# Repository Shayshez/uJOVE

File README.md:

# uJOVE
# CC BY-NC-SA 4.0
## Micro version of JOVE - Multimode filter, originally by System 80
## Warning for DIY beginners - this project is a hard to build with dense PCB and low pitch ic's which requires experience in SMD soldering.
### If you care about this project - DO NOT SELL ASSEMBLED MODULES, Build only for your own use!

Interactive BOM: http://diy.plum-audio.com/projects/uJove/iBom/

Plum Audio uJove is 8hp version of Jove - Multimode filter By System 80 that is inspired by the Roland Jupiter 6 filter.

uJuve is exactly the same circuit as the original 14 hp Juve with the same amazing sound. 

2 extra modifications have been added to increase the sound variety:

1. When no jack is plugged in to input 2 Positive feedback from the output to input 2 is activated. the feedback level can be controlled by LEVEL 2 knob.
2. Input 2 level knob can add 6dB of gain, 0dB on the middle, +6dB (clipping) when fully clockwise. 

4 Leds of the original 14 hp Jove replaced by one RGB Led

Modes colours:
RED - LP24 , ORANGE - LP12 , BLUE - BP , GREEN - HP

### About Positive Feedback:
Resonance = inverted feedback 

Positive feedback should distort the signal.

In LP2/4 modes (red/orange) the positive feedback alone can make pulses.

it’s better to mix between positive and negative feedback to achieve distorted worm sound.
Also try to use input 2 in LP modes and the positive feedback become clipper (attenuation until middle position of the knob and clipping from middle position)

The positive feedback sounds much better in BP/HP modes (blue/green) to achive great distortion.

uJove is available only as DIY project, for pcb's and panels: https://pushermanproductions.com/product/plum-audio-ujove-pcb-and-8hp-aluminium-panel/

Assembling Video (Part 1): https://www.youtube.com/watch?v=_F6PMT1OO5I

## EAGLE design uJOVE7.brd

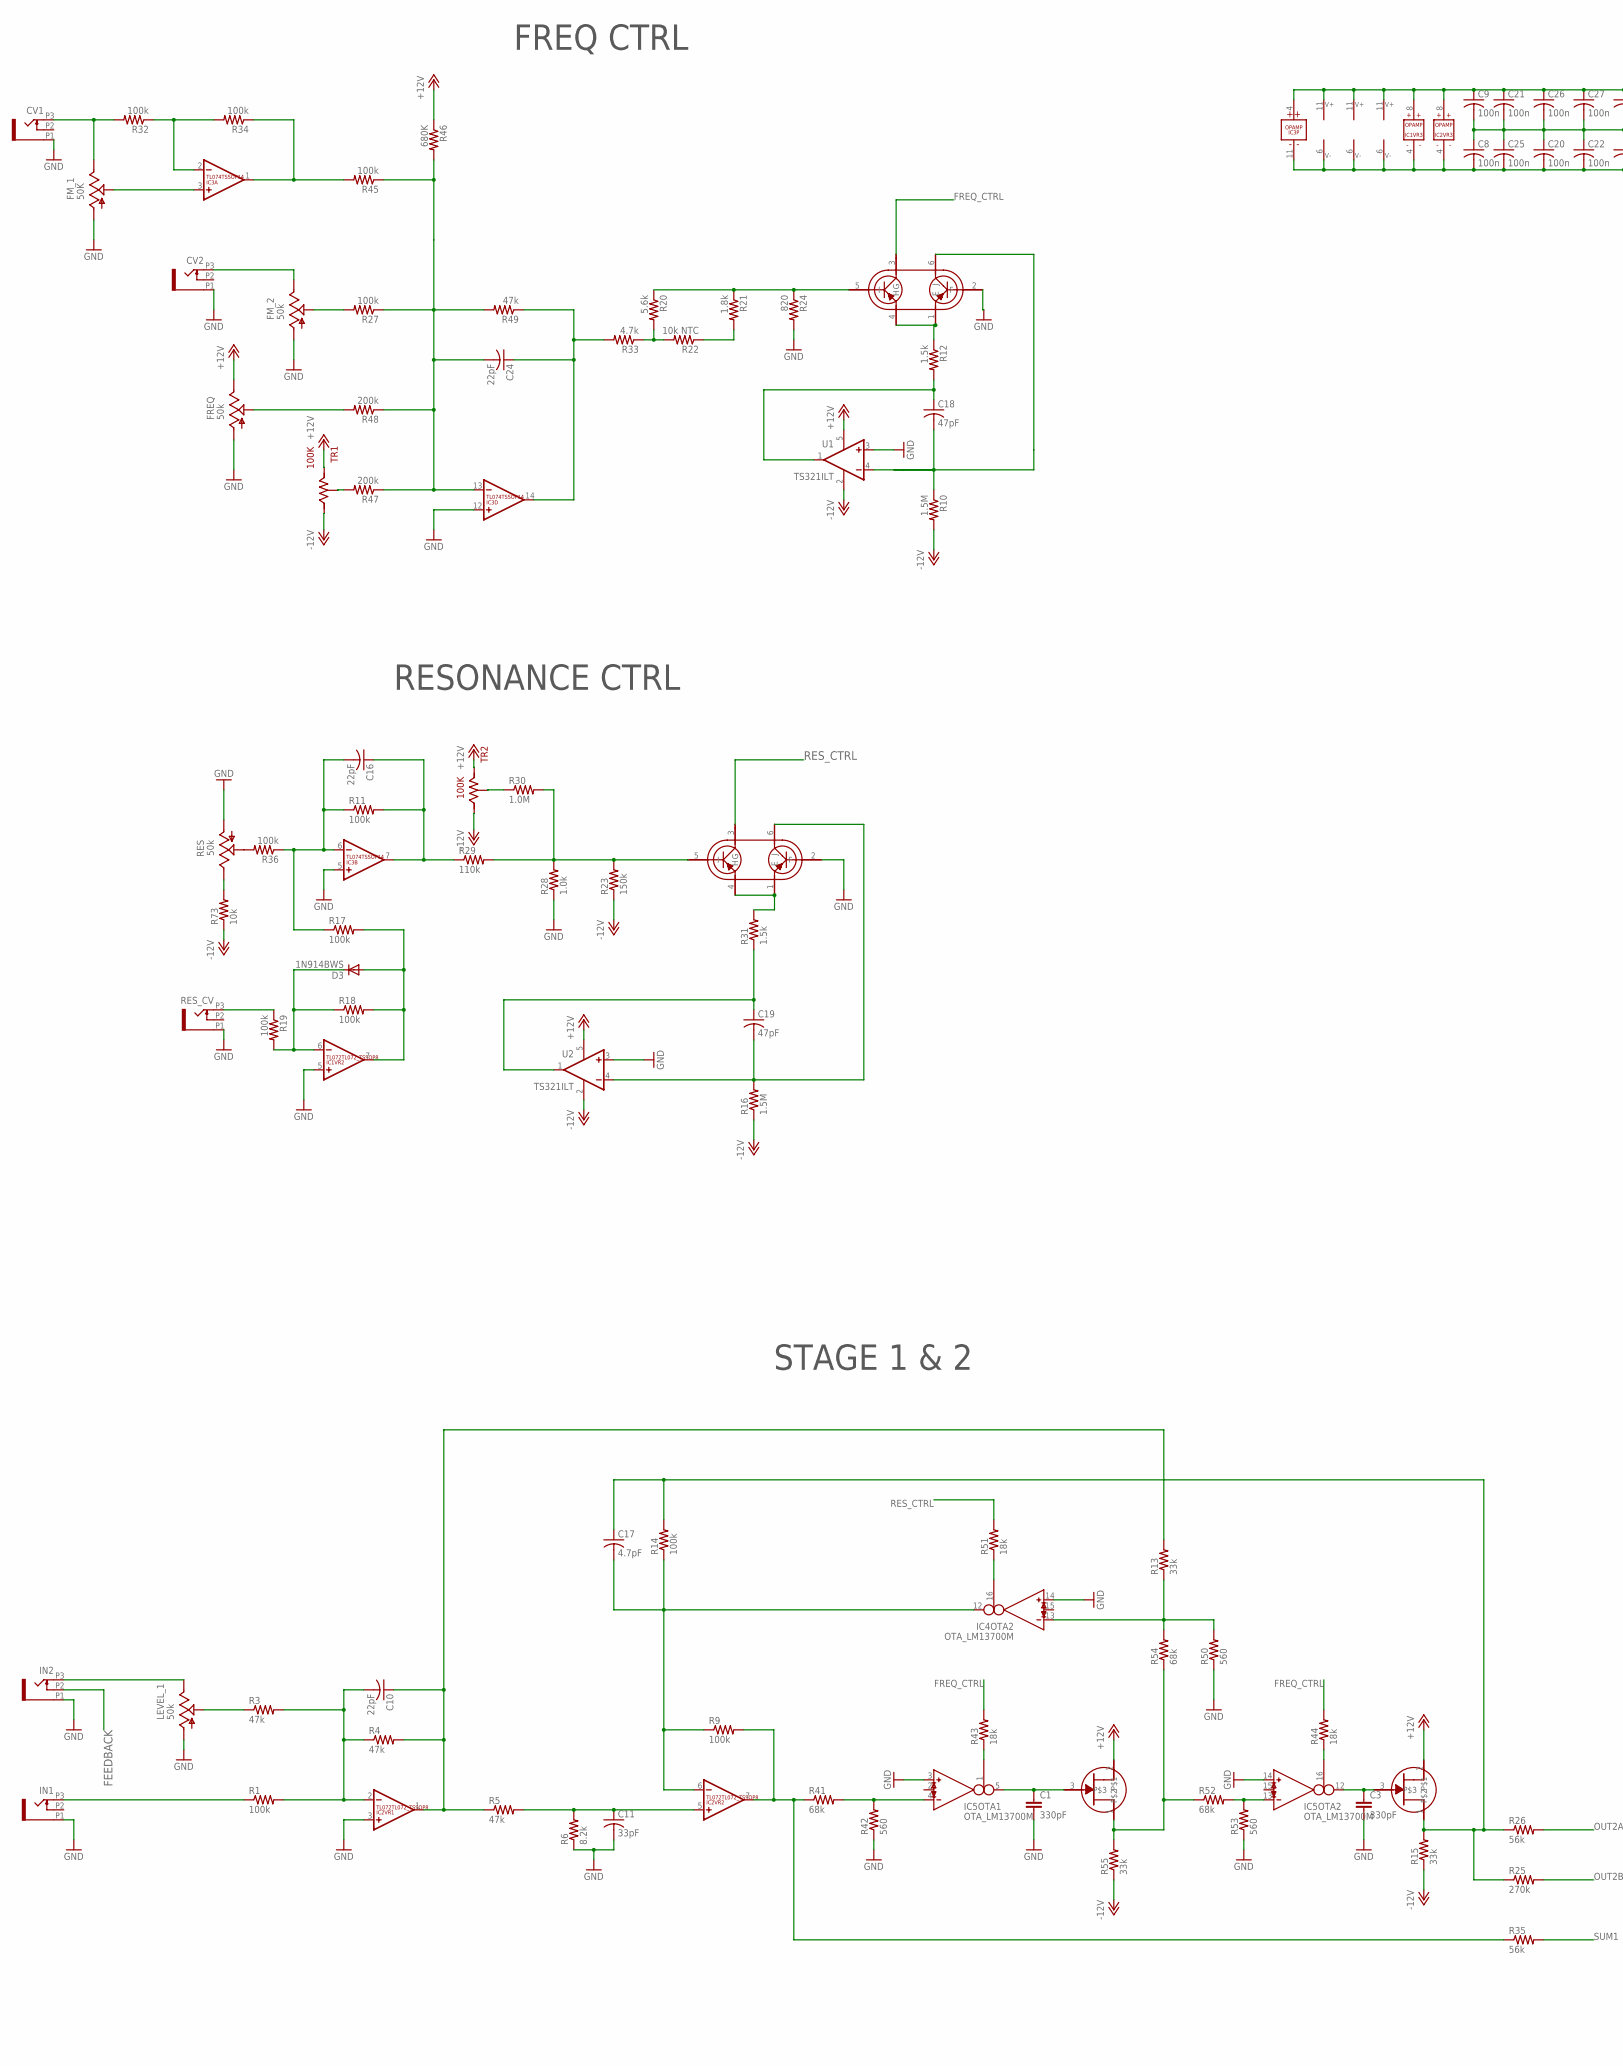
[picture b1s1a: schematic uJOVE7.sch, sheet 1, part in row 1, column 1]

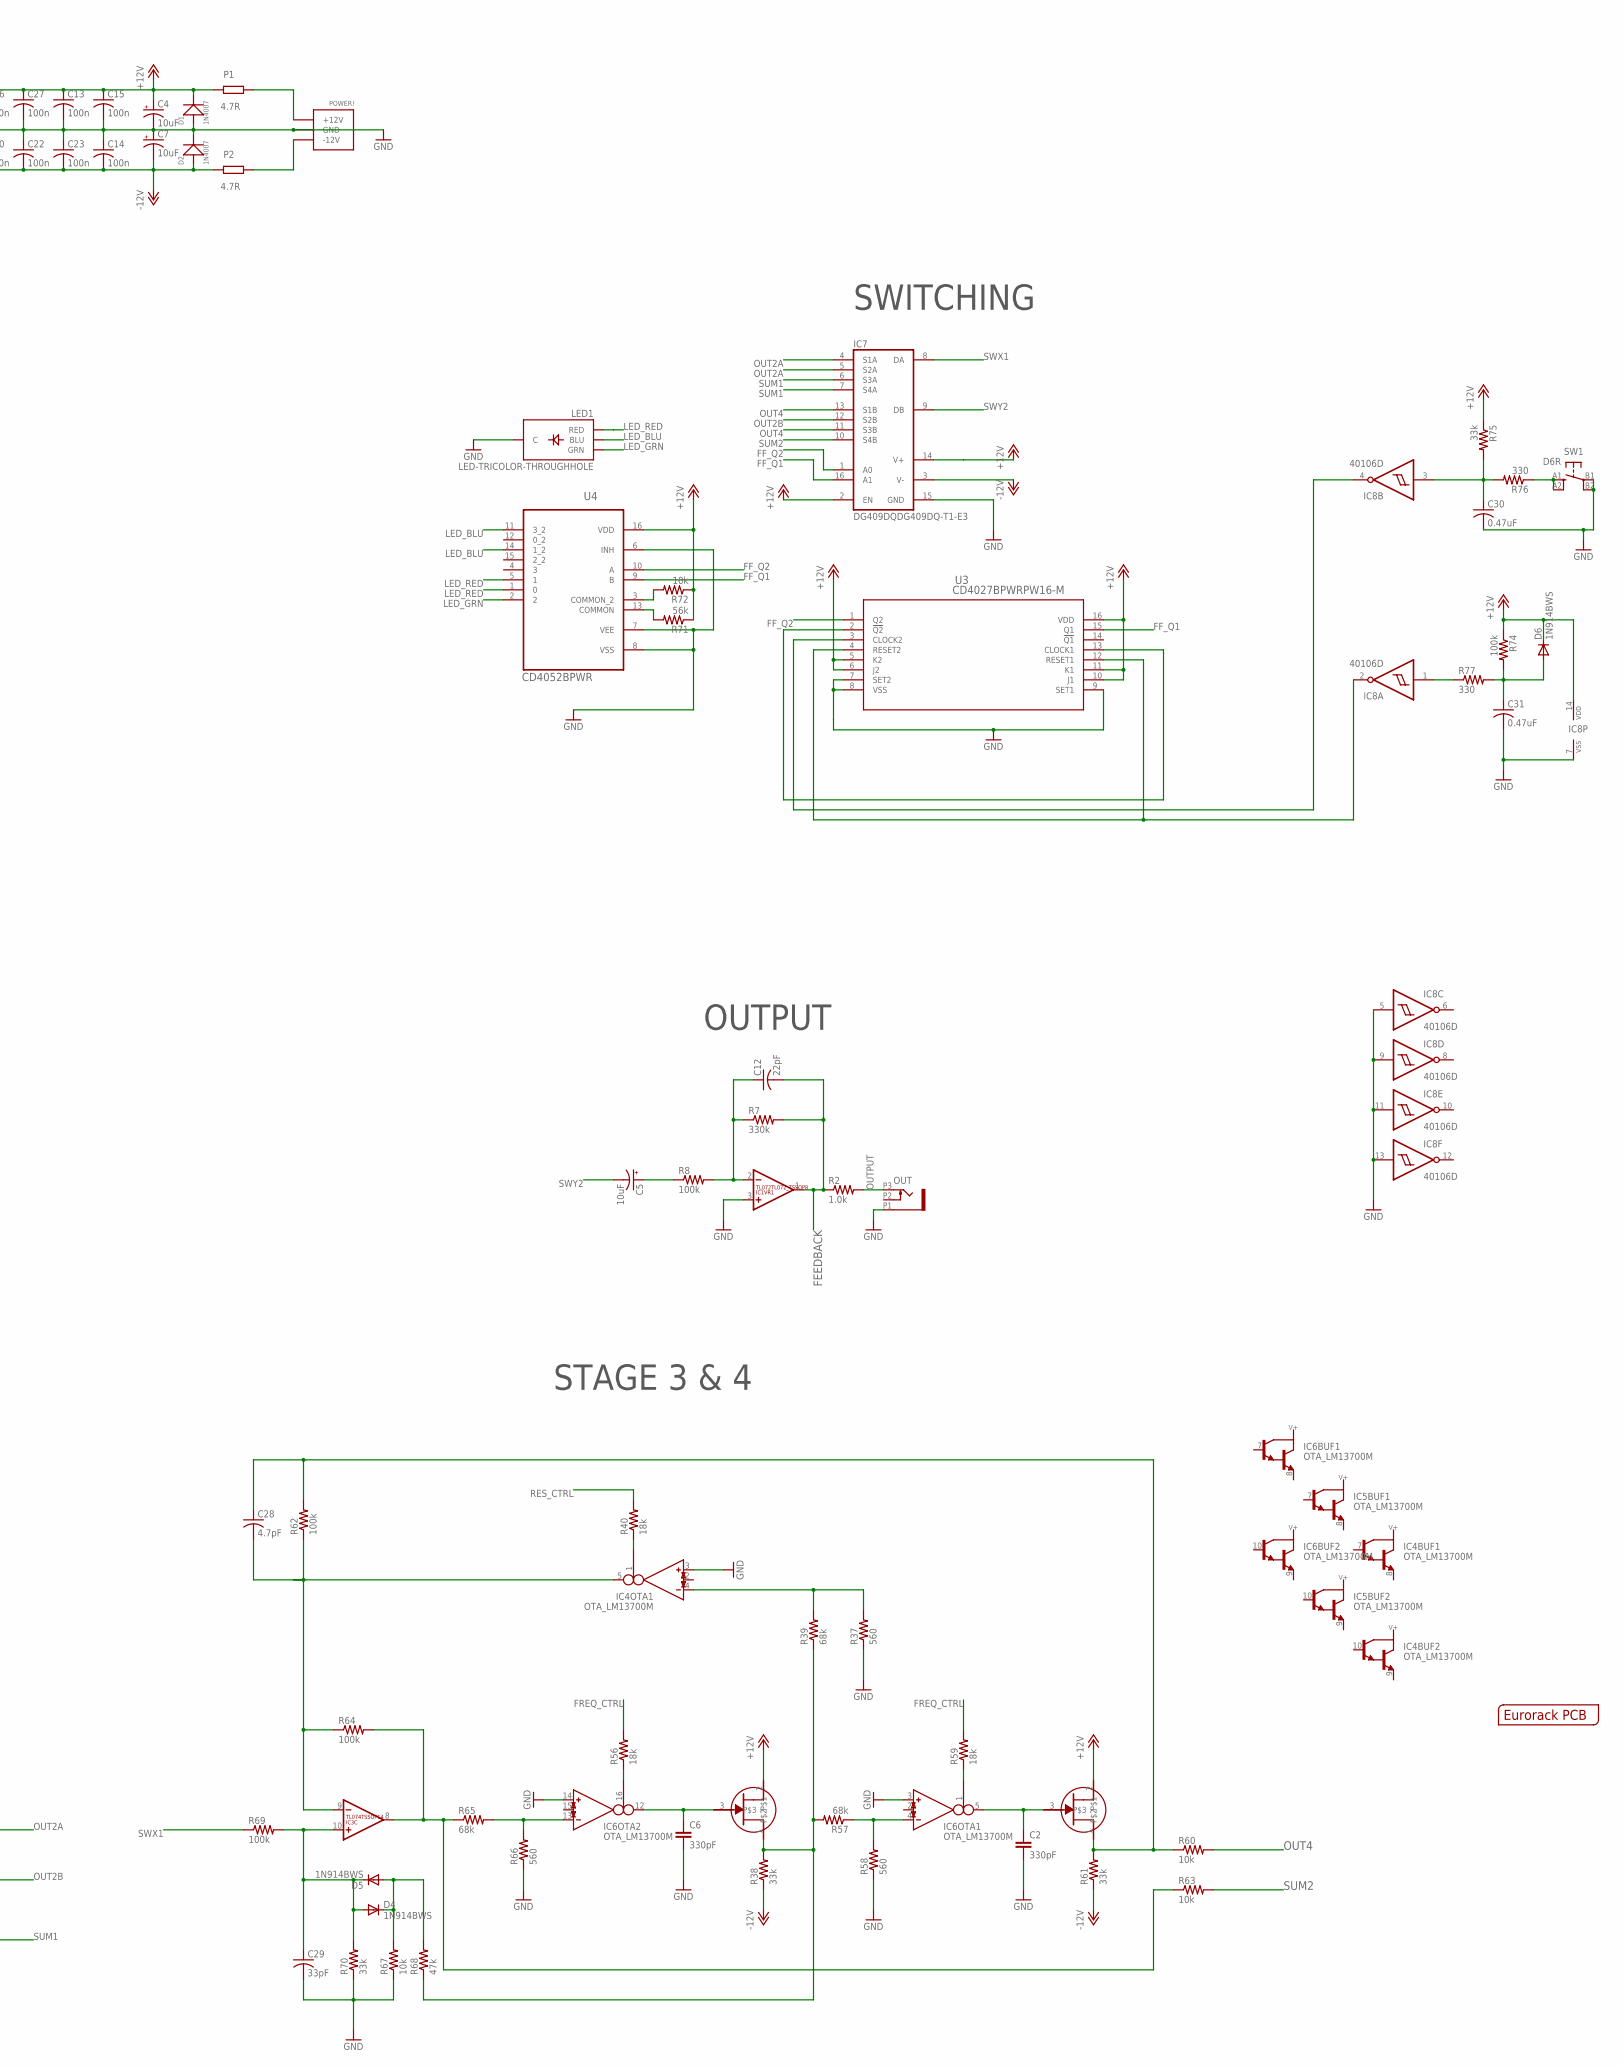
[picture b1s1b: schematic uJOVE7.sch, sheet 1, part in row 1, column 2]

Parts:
C1, C2, C3, C6: 330pF; C5B5
C4, C5, C7: 10uF; PANASONIC_C
C8, C9, C13, C14, C15, C20, C21, C22, C23, C25, C26, C27: 100n; C0603
C10, C12, C16, C24: 22pF; C0603
C11, C29: 33pF; C0603
C17, C28: 4.7pF; C0603
C18, C19: 47pF; C0603
C30, C31: 0.47uF; C0603
CV1, CV2: OG-PJ301_PJ301_THONKICONN; OG-PJ301_WQP_PJ_301M6_NO_HOLE
D1, D2: 1N4007; DO-214AC
D3, D4, D5, D6: 1N914BWS; SOD323-R
FM_1: 50K; OG-POTS_ALPS_POT_VERTICAL
FM_2: 50k; OG-POTS_ALPS_POT_VERTICAL
FREQ: 50k; OG-POTS_ALPS_POT_VERTICAL_PS
IC1, IC2: TL072TL072_TSSOP8; TL072_TSSOP8
IC3: TL074TSSOP14; TSSOP14
IC4, IC5, IC6: OTA_LM13700M; OTA_SO16
IC7: DG409DQDG409DQ-T1-E3; TSSOP16
IC8: 40106D; SO14
IN1, IN2: OG-PJ301_PJ301_THONKICONN; OG-PJ301_WQP_PJ_301M6_NO_HOLE
LED1: LED-TRICOLOR-THROUGHHOLE
LEVEL_1: 50k; OG-POTS_ALPS_POT_VERTICAL
OUT: OG-PJ301_PJ301_THONKICONN; OG-PJ301_WQP_PJ_301M6_NO_HOLE
P1, P2: 4.7R; R1206
PCB1: EURORACK_PCB; EURORACK8HPPCB-S
POWER!: POWER_SIMPLE; 2X05_SMT_HEADER
Q1, Q2: BCM857BS; SOT65P210X110-6N
Q3, Q4, Q5, Q6: MMBFJ112MMBFJ112; SOT23
R1, R8, R9, R11, R14, R17, R18, R19, R27, R32, R34, R36, R45, R62, R64, R69, R74: 100k; R0603
R2, R28: 1.0k; R0603
R3, R4, R5, R49, R68: 47k; R0603
R6: 8.2k; R0603
R7: 330k; R0603
R10, R16: 1.5M; R0603
R12, R31: 1.5k; R0603
R13, R15, R38, R55, R61, R70, R75: 33k; R0603
R20: 5.6k; R0603
R21: 1.8k; R0603
R22: 10k NTC; R0805
R23: 150k; R0603
R24: 820; R0603
R25: 270k; R0603
R26, R35, R71: 56k; R0603
R29: 110k; R0603
R30: 1.0M; R0603
R33: 4.7k; R0603
R37, R42, R50, R53, R58, R66: 560; R0603
R39, R41, R52, R54, R57, R65: 68k; R0603
R40, R43, R44, R51, R56, R59: 18k; R0603
R46: 680K; R0603
R47, R48: 200k; R0603
R60, R63, R67, R72, R73: 10k; R0603
R76, R77: 330; R0603
RES: 50k; OG-POTS_ALPS_POT_VERTICAL_PS
RES_CV: OG-PJ301_PJ301_THONKICONN; OG-PJ301_WQP_PJ_301M6_NO_HOLE
SW1: D6R
TR1, TR2: 100K; TC33X-2
U1, U2: TS321ILT; SOT23-5
U3: CD4027BPWRPW16-M; PW16-M
U4: CD4052BPWR; SOP65P640X120-16N

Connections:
+12V: C4.+, C9.1, C13.1, C15.1, C21.1, C26.1, C27.1, D1.2 (-), D6.C, FREQ.P$1 (E), IC1.8 (V+), IC2.8 (V+), IC3.4 (V+), IC4.11 (V+), IC5.11 (V+), IC6.11 (V+), IC7.2 (EN), IC7.14 (V+), IC8.14 (VDD), P1.1, Q3.2, Q4.2, Q5.2, Q6.2, R46.1, R71.1, R72.1, R74.1, R75.1, TR1.1, TR2.1, U1.5 (V+), U2.5 (V+), U3.5 (K2), U3.6 (J2), U3.10 (J1), U3.11 (K1), U3.16 (VDD), U4.16 (VDD)
-12V: C7.-, C8.2, C14.2, C20.2, C22.2, C23.2, C25.2, D2.1 (+), IC1.4 (V-), IC2.4 (V-), IC3.11 (V-), IC4.6 (V-), IC5.6 (V-), IC6.6 (V-), IC7.3 (V-), P2.1, R10.2, R15.1, R16.1, R23.1, R38.1, R55.1, R61.1, R73.1, TR1.3, TR2.3, U1.2 (V-), U2.2 (V-)
FEEDBACK: C12.2, IC1.1 (OUT), IN2.P2 (2), R2.1, R7.2
FF_Q1: IC7.16 (A1), U3.15 (Q1), U4.9 (B)
FF_Q2: IC7.1 (A0), U3.1 (Q2), U4.10 (A)
FREQ_CTRL: Q1.3 (G), R43.2, R44.2, R56.2, R59.2
GND: C1.2, C2.2, C3.2, C4.-, C6.2, C7.+, C8.1, C9.2, C11.2, C13.2, C14.1, C15.2, C20.1, C21.2, C22.1, C23.1, C25.1, C26.2, C27.2, C29.2, C30.2, C31.2, CV1.P1 (1), CV2.P1 (1), D1.1 (+), D2.2 (-), FM_1.P$3 (A), FM_2.P$3 (A), FREQ.P$3 (A), IC1.3 (+IN), IC1.5 (+IN), IC2.3 (+IN), IC3.5 (+IN), IC3.12 (+IN), IC4.3 (IN_P), IC4.14 (IN_P), IC5.3 (IN_P), IC5.14 (IN_P), IC6.3 (IN_P), IC6.14 (IN_P), IC7.15 (GND), IC8.5 (I), IC8.7 (VSS), IC8.9 (I), IC8.11 (I), IC8.13 (I), IN1.P1 (1), IN2.P1 (1), LED1.GND (C), LEVEL_1.P$3 (A), OUT.P1 (1), POWER!.3 (GND), POWER!.4 (GND), POWER!.5 (GND), POWER!.6 (GND), POWER!.7 (GND), POWER!.8 (GND), Q1.2 (F), Q2.2 (F), R6.1, R24.2, R28.1, R37.1, R42.1, R50.1, R53.1, R58.1, R66.1, R67.1, R70.1, RES.P$3 (A), RES_CV.P1 (1), SW1.B1, SW1.B2 (P1), U1.3 (+IN), U2.3 (+IN), U3.7 (SET2), U3.8 (VSS), U3.9 (SET1), U4.6 (INH), U4.7 (VEE), U4.8 (VSS)
LED_BLU: LED1.BLU, U4.11 (3_2), U4.14 (1_2)
LED_GRN: LED1.GRN, U4.2
LED_RED: LED1.RED, U4.1 (0), U4.5 (1)
unnamed: P1.2, POWER!.9 (+12V), POWER!.10 (+12V)
unnamed: P2.2, POWER!.1 (-12V), POWER!.2 (-12V)
unnamed: IN1.P3 (3), R1.1
unnamed: C10.2, IC2.2 (-IN), R1.2, R3.2, R4.1
unnamed: IN2.P3 (3), LEVEL_1.P$1 (E)
unnamed: LEVEL_1.P$2 (S), R3.1
unnamed: C10.1, IC2.1 (OUT), R4.2, R5.1, R13.2
unnamed: C11.1, IC2.5 (+IN), R5.2, R6.2
unnamed: IC2.7 (OUT), R9.2, R35.1, R41.1
unnamed: C17.2, IC2.6 (-IN), IC4.12 (OUT), R9.1, R14.1
unnamed: IC5.4 (IN_N), R41.2, R42.2
unnamed: IC5.1 (I_BIAS), R43.1
unnamed: C1.1, IC5.5 (OUT), Q4.3
unnamed: IC5.13 (IN_N), R52.2, R53.2
unnamed: IC4.13 (IN_N), R13.1, R50.2, R54.2
unnamed: IC4.16 (I_BIAS), R51.1
unnamed: C17.1, Q3.1, R14.2, R15.2, R25.1, R26.1
unnamed: Q4.1, R52.1, R54.1, R55.2
unnamed: IC5.16 (I_BIAS), R44.1
unnamed: R73.2, RES.P$1 (E)
unnamed: C3.1, IC5.12 (OUT), Q3.3
unnamed: C5.+, R8.1
unnamed: C12.1, IC1.2 (-IN), R7.1, R8.2
unnamed: C31.1, D6.A, R74.2, R77.2
unnamed: IC3.8 (OUT), R63.1, R64.2, R65.1
unnamed: IC6.4 (IN_N), R57.1, R58.2
unnamed: D4.C, D5.A, R67.2, R68.2
unnamed: C29.1, D4.A, D5.C, IC3.10 (+IN), R69.2, R70.2
unnamed: IC6.13 (IN_N), R65.2, R66.2
unnamed: IC4.4 (IN_N), R37.2, R39.2
unnamed: IC6.16 (I_BIAS), R56.1
unnamed: C6.1, IC6.12 (OUT), Q6.3
unnamed: Q6.1, R38.2, R39.1, R57.2, R68.1
unnamed: IC4.1 (I_BIAS), R40.1
unnamed: C28.2, IC3.9 (-IN), IC4.5 (OUT), R62.1, R64.1
unnamed: R36.2, RES.P$2 (S)
unnamed: IC6.1 (I_BIAS), R59.1
unnamed: C28.1, Q5.1, R60.1, R61.2, R62.2
unnamed: C2.1, IC6.5 (OUT), Q5.3
unnamed: R19.1, RES_CV.P3 (3)
unnamed: D3.C, IC1.6 (-IN), R18.1, R19.2
unnamed: D3.A, IC1.7 (OUT), R17.2, R18.2
unnamed: C16.2, IC3.6 (-IN), R11.1, R17.1, R36.1
unnamed: R30.1, TR2.2
unnamed: C16.1, IC3.7 (OUT), R11.2, R29.1
unnamed: Q2.5 (I), R23.2, R28.2, R29.2, R30.2
unnamed: Q2.1 (E), Q2.4 (H), R31.2
unnamed: C19.2, Q2.6 (J), R16.2, U2.4 (-IN)
unnamed: C19.1, R31.1, U2.1 (OUT)
unnamed: CV1.P3 (3), FM_1.P$1 (E), R32.2
unnamed: IC3.2 (-IN), R32.1, R34.2
unnamed: FM_1.P$2 (S), IC3.3 (+IN)
unnamed: IC3.1 (OUT), R34.1, R45.2
unnamed: C24.2, IC3.13 (-IN), R27.1, R45.1, R46.2, R47.1, R48.1, R49.2
unnamed: CV2.P3 (3), FM_2.P$1 (E)
unnamed: FM_2.P$2 (S), R27.2
unnamed: FREQ.P$2 (S), R48.2
unnamed: R47.2, TR1.2
unnamed: C24.1, IC3.14 (OUT), R33.2, R49.1
unnamed: R20.2, R22.2, R33.1
unnamed: Q1.5 (I), R20.1, R21.1, R24.1
unnamed: R21.2, R22.1
unnamed: C18.2, Q1.6 (J), R10.1, U1.4 (-IN)
unnamed: Q1.1 (E), Q1.4 (H), R12.1
unnamed: C18.1, R12.2, U1.1 (OUT)
unnamed: IC8.1 (I), R77.1
unnamed: C30.1, IC8.3 (I), R75.2, R76.2
unnamed: IC8.2 (O), U3.4 (RESET2), U3.12 (RESET1)
unnamed: IC8.4 (O), U3.3 (CLOCK2)
unnamed: R76.1, SW1.A1 (S), SW1.A2 (S1)
unnamed: U3.2 (!Q2), U3.13 (CLOCK1)
unnamed: R72.2, U4.3 (COMMON_2)
unnamed: R71.2, U4.13 (COMMON)
OUT2A: IC7.4 (S1A), IC7.5 (S2A), R26.2
OUT2B: IC7.12 (S2B), R25.2
OUT4: IC7.11 (S3B), IC7.13 (S1B), R60.2
OUTPUT: OUT.P3 (3), R2.2
RES_CTRL: Q2.3 (G), R40.2, R51.2
SUM1: IC7.6 (S3A), IC7.7 (S4A), R35.2
SUM2: IC7.10 (S4B), R63.2
SWX1: IC7.8 (DA), R69.1
SWY2: C5.-, IC7.9 (DB)

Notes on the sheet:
STAGE 1 & 2
OUTPUT
STAGE 3 & 4
RESONANCE CTRL
FREQ CTRL
SWITCHING

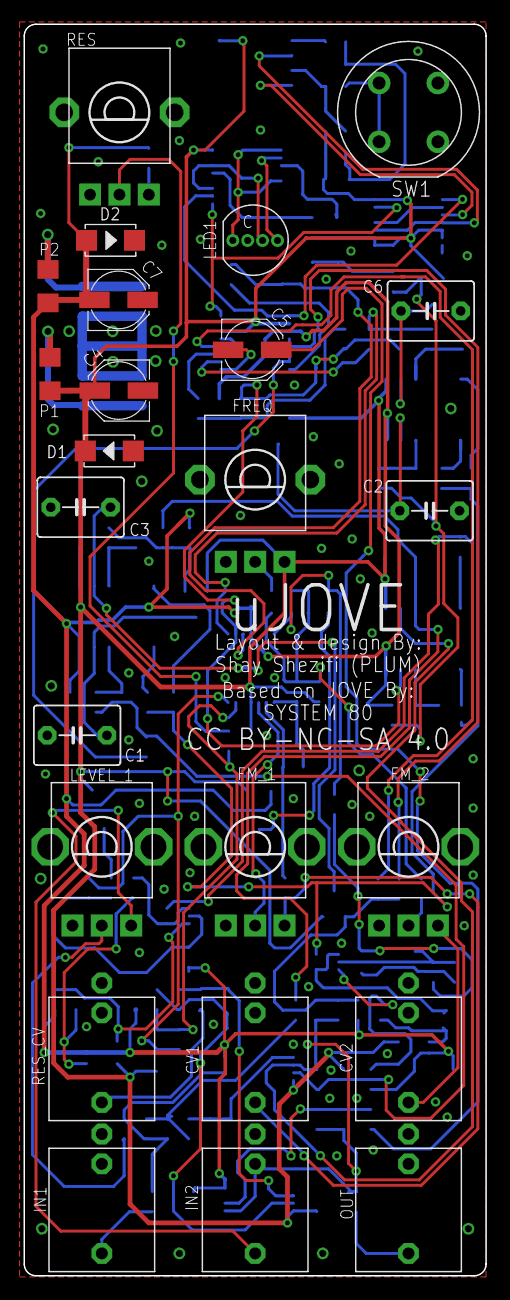
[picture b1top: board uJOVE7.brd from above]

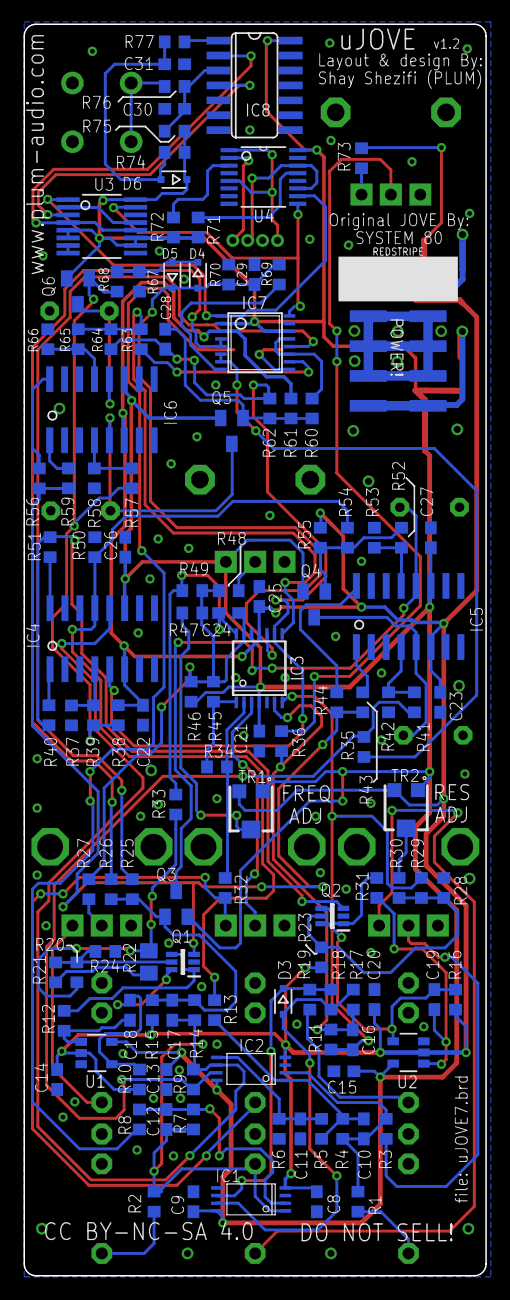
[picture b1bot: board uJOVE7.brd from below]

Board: 2 copper layers, 39.3 x 106.5 mm, 151 parts (126 on the bottom side), 92 nets.

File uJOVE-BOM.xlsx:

Qty | Parts | Value | Device | Package | Mouser referance | Description
 | CAPS
2 | C15, C26 | 4.7pF | C-USC0603 | C0603 | CC0603CRNPO9BN4R7 | CAPACITOR, American symbol
4 | C8, C10, C14, C22 | 22pF | C-USC0603 | C0603 | C0603C220J5G7411 | CAPACITOR, American symbol
2 | C9, C27 | 33pF | C-USC0603 | C0603 | C0603C330J5GACTU | CAPACITOR, American symbol
2 | C16, C17 | 47pF | C-USC0603 | C0603 | C0603C470J5GACTU | CAPACITOR, American symbol
10 | C11, C12, C13, C18, C19, C20, C21, C23, C24, C25 | 100n | C-USC0603 | C0603 | C0603C104M5RACTU | CAPACITOR, American symbol
2 | C28, C29 | 0.47uF | C-USC0603 | C0603 | CGA3E3X5R1H474MB | CAPACITOR, American symbol
1 | C5 | 10uF | CPOL-USC | PANASONIC_C | UUQ1E100MCL1GB | POLARIZED CAPACITOR, American symbol
2 | C4, C7 | 10uF | CPOL-USC | PANASONIC_C | EEE-1EA100SR | POLARIZED CAPACITOR, American symbol
4 | C1, C2, C3, C6 | 330pF | C5/5 | C5B5 | PFR5331J100J11L4 | Polypropylene FILM CAPACITOR 5mm
 | RESISTORS
2 | R76, R77 | 330 | R-US_R0603 | R0603 | RC0603FR-07330RL | RESISTOR, American symbol
6 | R37, R42, R50, R53, R57, R65 | 560 | R-US_R0603 | R0603 | RC0603FR-07560RL | RESISTOR, American symbol
1 | R24 | 820 | R-US_R0603 | R0603 | RC0603FR-07820RL | RESISTOR, American symbol
2 | R2, R28 | 1.0k | R-US_R0603 | R0603 | RC0603FR-071KL | RESISTOR, American symbol
2 | R12, R31 | 1.5k | R-US_R0603 | R0603 | RC0603FR-071K5L | RESISTOR, American symbol
1 | R21 | 1.8k | R-US_R0603 | R0603 | RC0603FR-071K8L | RESISTOR, American symbol
1 | R33 | 4.7k | R-US_R0603 | R0603 | RC0603FR-074K7L | RESISTOR, American symbol
1 | R20 | 5.6k | R-US_R0603 | R0603 | RC0603FR-105K6L | RESISTOR, American symbol
1 | R6 | 8.2k | R-US_R0603 | R0603 | RC0603FR-078K2L | RESISTOR, American symbol
5 | R59, R62, R67, R72, R73 | 10k | R-US_R0603 | R0603 | RC0603FR-0710KL | RESISTOR, American symbol
6 | R40, R43, R44, R51, R58, R66 | 18k | R-US_R0603 | R0603 | RC0603FR-0718KL | RESISTOR, American symbol
7 | R13, R15, R38, R55, R60, R70, R75 | 33k | R-US_R0603 | R0603 | RC0603FR-0733KL | RESISTOR, American symbol
5 | R3, R4, R5, R49, R68 | 47k | R-US_R0603 | R0603 | RC0603FR-0747KL | RESISTOR, American symbol
3 | R26, R35, R71 | 56k | R-US_R0603 | R0603 | RC0603FR-0756KL | RESISTOR, American symbol
6 | R39, R41, R52, R54, R56, R64 | 68k | R-US_R0603 | R0603 | RC0603FR-0768KL | RESISTOR, American symbol
17 | R1, R8, R9, R11, R14, R17, R18, R19, R27, R32, R34, R36, R45, R61, R63, R69, R74 | 100k | R-US_R0603 | R0603 | RC0603FR-07100KL | RESISTOR, American symbol
1 | R29 | 110k | R-US_R0603 | R0603 | RC0603FR-07110KL | RESISTOR, American symbol
1 | R23 | 150k | R-US_R0603 | R0603 | RC0603FR-07150KL | RESISTOR, American symbol
2 | R47, R48 | 200k | R-US_R0603 | R0603 | RC0603FR-07200KL | RESISTOR, American symbol
1 | R25 | 270k | R-US_R0603 | R0603 | RC0603FR-07270KL | RESISTOR, American symbol
1 | R7 | 330k | R-US_R0603 | R0603 | RC0603FR-07330KL | RESISTOR, American symbol
1 | R46 | 680K | R-US_R0603 | R0603 | RC0603FR-07680KL | RESISTOR, American symbol
1 | R30 | 1.0M | R-US_R0603 | R0603 | RC0603FR-071ML | RESISTOR, American symbol
2 | R10, R16 | 1.5M | R-US_R0603 | R0603 | RC0603FR-071M5L | RESISTOR, American symbol
1 | R22 | 10k NTC | R-US_R0805 | R0805 | NCP21XV103J03RA | RESISTOR, American symbol
 | Note1: R71 & R72 = led brightness, R71 for green, R72 for red & blue.
 | Note2: R3 = Gain of input 2 and feadback, 47k for 0dB at pot middle position an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
 | DIODES / TRANSISTORS
2 | P1, P2 | PTCSMD | PTCSMD | PTC-1206 | 1206L035/16YR | Resettable Fuse PTC
4 | D3, D4, D5, D6 | 1N914BWS | DIODE-SOD323-R | SOD323-R | 512-1N914BWS | DIODE
2 | D1, D2 | S1BB | DIODE-GEN-PURPOSE-1KV-1A(DO-214AC) | DO-214AC | 621-S1BB-F | 304010013
2 | Q1, Q2 | BCM857BS | BCM857BS | SOT65P210X110-6N | BC857BS-7-F | NEXPERIA - BCM857BS - TRANSISTOR, MATCHED, SOT-363
4 | Q3, Q4, Q5, Q6 | MMBFJ112MMBFJ112 | MMBFJ112MMBFJ112 | SOT23 | 512-MMBFJ112 | * NO STOCK AT MOUSER, CAN BE FOUND HERE: https://www.aliexpress.com/item/FREE-S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
 | IC'S
1 | IC7 | 40106D | 40106D | SO14 | CD40106BM96 | Hex SCHMITT TRIGGER
1 | U4 | CD4052BPWR | CD4052BPWR | SOP65P640X120-16N | CD4052BPWR | single 8-Channel multiplexer
2 | U1, U2 | TS321ILT | TS321IDBV | SOT23-5 | TS321ILT
2 | IC1, IC2 | TL074TSSOP14 | TL074TSSOP14 | TSSOP14 | TL074CPWR | OP AMP
1 | IC6 | DQDG409DQ-T1-E3 | DG409DQ-T1-E3 | TSSOP16 | DG409DQ-E3 | ANALOG MULTIPLEXER
3 | IC3, IC4, IC5 | OTA_LM13700M | OTA_LM13700M | OTA_SO16 | LM13700MX/NOPB | Dual OTA with buffers
1 | U3 | CD4027BPWRPW16-M | CD4027BPWRPW16-M | PW16-M | CD4027BPWR
 | TH / MISC
2 | TR1, TR2 | 100K | TC33X-2-104E | TC33X-2 | TC33X-2-104E | Cermet 3mm SMT trimmer,0.1W 100k Bourns TC33 Series SMD Cermet Trimmer Resistor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
1 | LED1 | LED-TRICOLOR-THROUGHHOLE | LED-TRICOLOR-THROUGHHOLE | LED-TRICOLOR-THROUGHHOLE | COMON CATHODE | https://www.aliexpress.com/item/50-pcs-LED-5mm-RGB-Diffused-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
1 | SW1 | D6R | D6R | D6R | KS-01Q-01 | C&K D6R
6 | CV1, CV2, IN1, IN2, OUT, RES_CV | PJ301_PJ301_THONKICONN | THONKICONN | PJ301_WQP_PJ_301M6 | https://www.thonk.co.uk/shop/thonkiconn/
3 | FM_1, FM_2, LEVEL_2 | B50k | Song Huei Tall trimmer 9mm |  | https://www.thonk.co.uk/shop/ttpots/
2 | FREQ, RES | B50k | Alpha 9mm Pot |  | https://www.thonk.co.uk/shop/alpha-9mm-pots-vertical-t18/
1 | POWER! | SMD POWER HEADER | POWER | 2X05_SMT_HEADER | https://www.ebay.com/itm/10pcs-2-40Pin-SMD-SMT-2-40Pin-Male-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
 | Big knob (Frequancy) | ‘MXR’ Style Knobs |  |  | https://www.thonk.co.uk/shop/mxr-style-knobs/
 | Resonance Knob | 1900h |  |  | https://www.thonk.co.uk/shop/1900h-t18/

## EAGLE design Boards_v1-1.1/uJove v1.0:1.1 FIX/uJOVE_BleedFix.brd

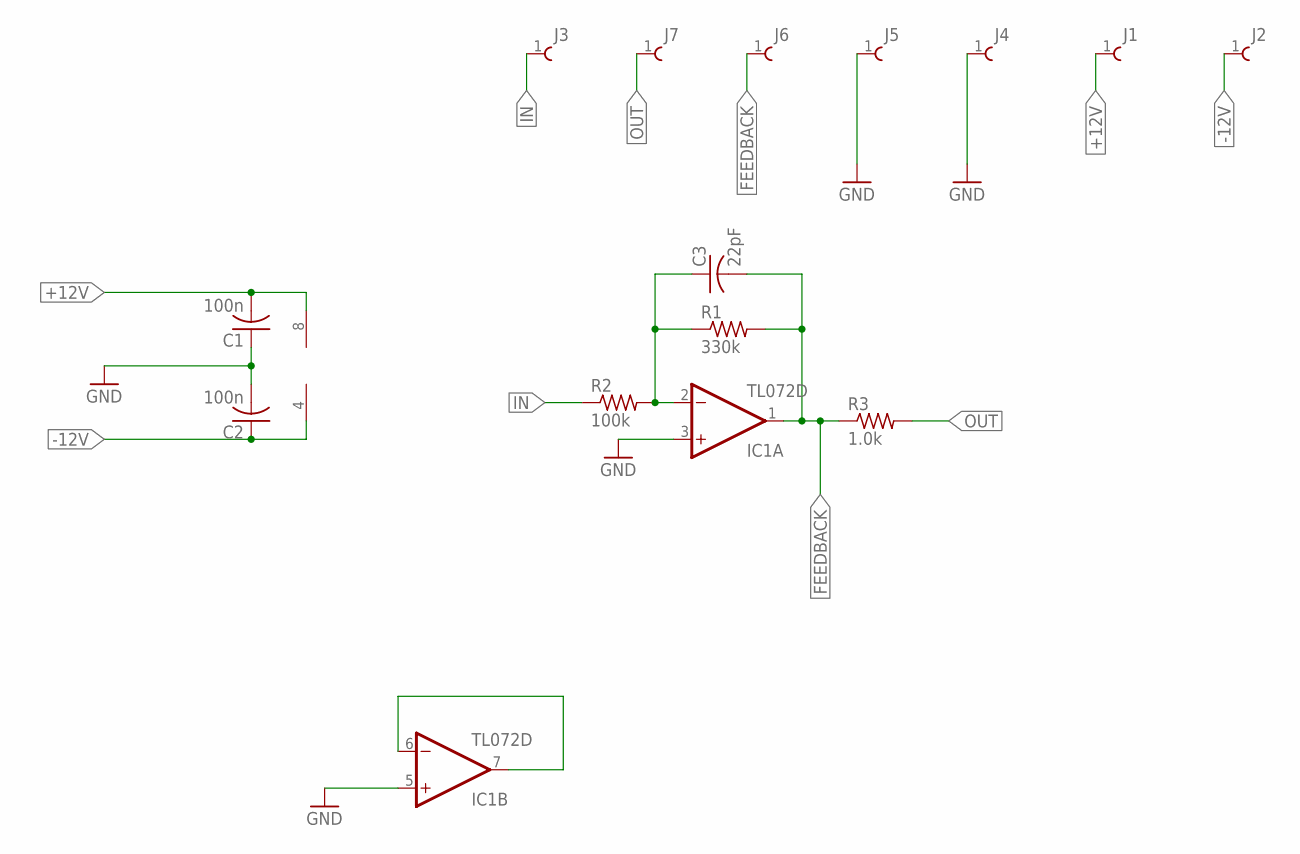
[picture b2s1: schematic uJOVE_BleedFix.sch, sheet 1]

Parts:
C1, C2: 100n; C0603
C3: 22pF; C0603
IC1: TL072D; SO08
J1, J2, J3, J4, J5, J6, J7: 61300111121
R1: 330k; R0603
R2: 100k; R0603
R3: 1.0k; R0603

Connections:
+12V: C1.2, IC1.8 (V+), J1.1
-12V: C2.1, IC1.4 (V-), J2.1
FEEDBACK: C3.2, IC1.1 (OUT), J6.1, R1.2, R3.1
GND: C1.1, C2.2, IC1.3 (+IN), IC1.5 (+IN), J4.1, J5.1
IN: J3.1, R2.1
unnamed: IC1.6 (-IN), IC1.7 (OUT)
unnamed: C3.1, IC1.2 (-IN), R1.1, R2.2
OUT: J7.1, R3.2

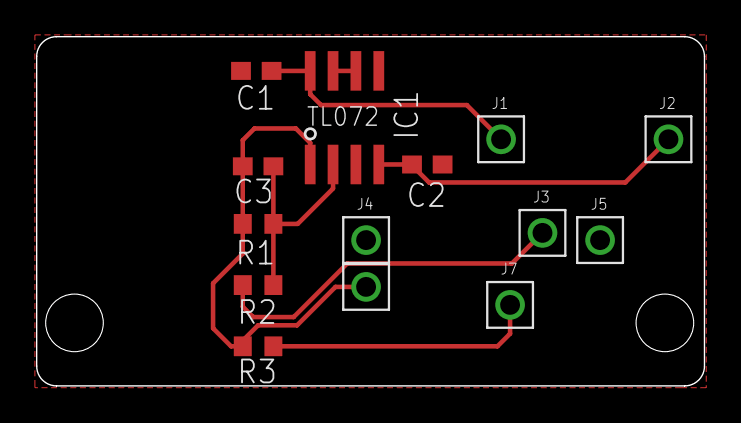
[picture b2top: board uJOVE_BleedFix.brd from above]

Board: 2 copper layers, 37.1 x 19.4 mm, 14 parts (0 on the bottom side), 8 nets.

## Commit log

2018-11-20 Initial release
2018-11-22 Updated BOM
2018-12-10 Fixed mouser reference
2019-09-02 Output bleed FIX for uJove v1.0/1.1
2019-10-01 Files for boards v1 or v1.1
2019-10-01 Board v1.2
2019-10-01 BOM uJove v1.2

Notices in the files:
parts and their libraries:
Wurth_Elektronik_Electromechanic_Board_t: Copyright: Würth Elektronik
